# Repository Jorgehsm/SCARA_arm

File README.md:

# SCARA robotic arm
Braço robótico com 4DOF baseado em esp32.

Utiliza motores de passo com redução por correia para movimento e servo MG996r para controle da pinça.

Projeto pessoal em desenvolvimento

## Projeto da placa de circuito
O projeto conta com o design de uma placa de circuitos para conectar o esp32 responsável pela comunicação e controle do robô com a alimentação e drivers dos motores.

## Projeto CAD
A estrutura do robô foi pensada para fabricação por meio de impressão 3D juntamente com fuso trapezoidal e eixos de aço para movimento no eixo Z.

A transmissão para demais movimentos foi feita por meio de correias GT2 e polias impressas

A estrutura conta também com rolamentos para adicionar rigidez e auxíliar nos movimentos.

O projeto conta também com o design de uma garra atuada por meio de um motor servo e mecanismo pinhâo cremalheira para sua abertura e fechamento

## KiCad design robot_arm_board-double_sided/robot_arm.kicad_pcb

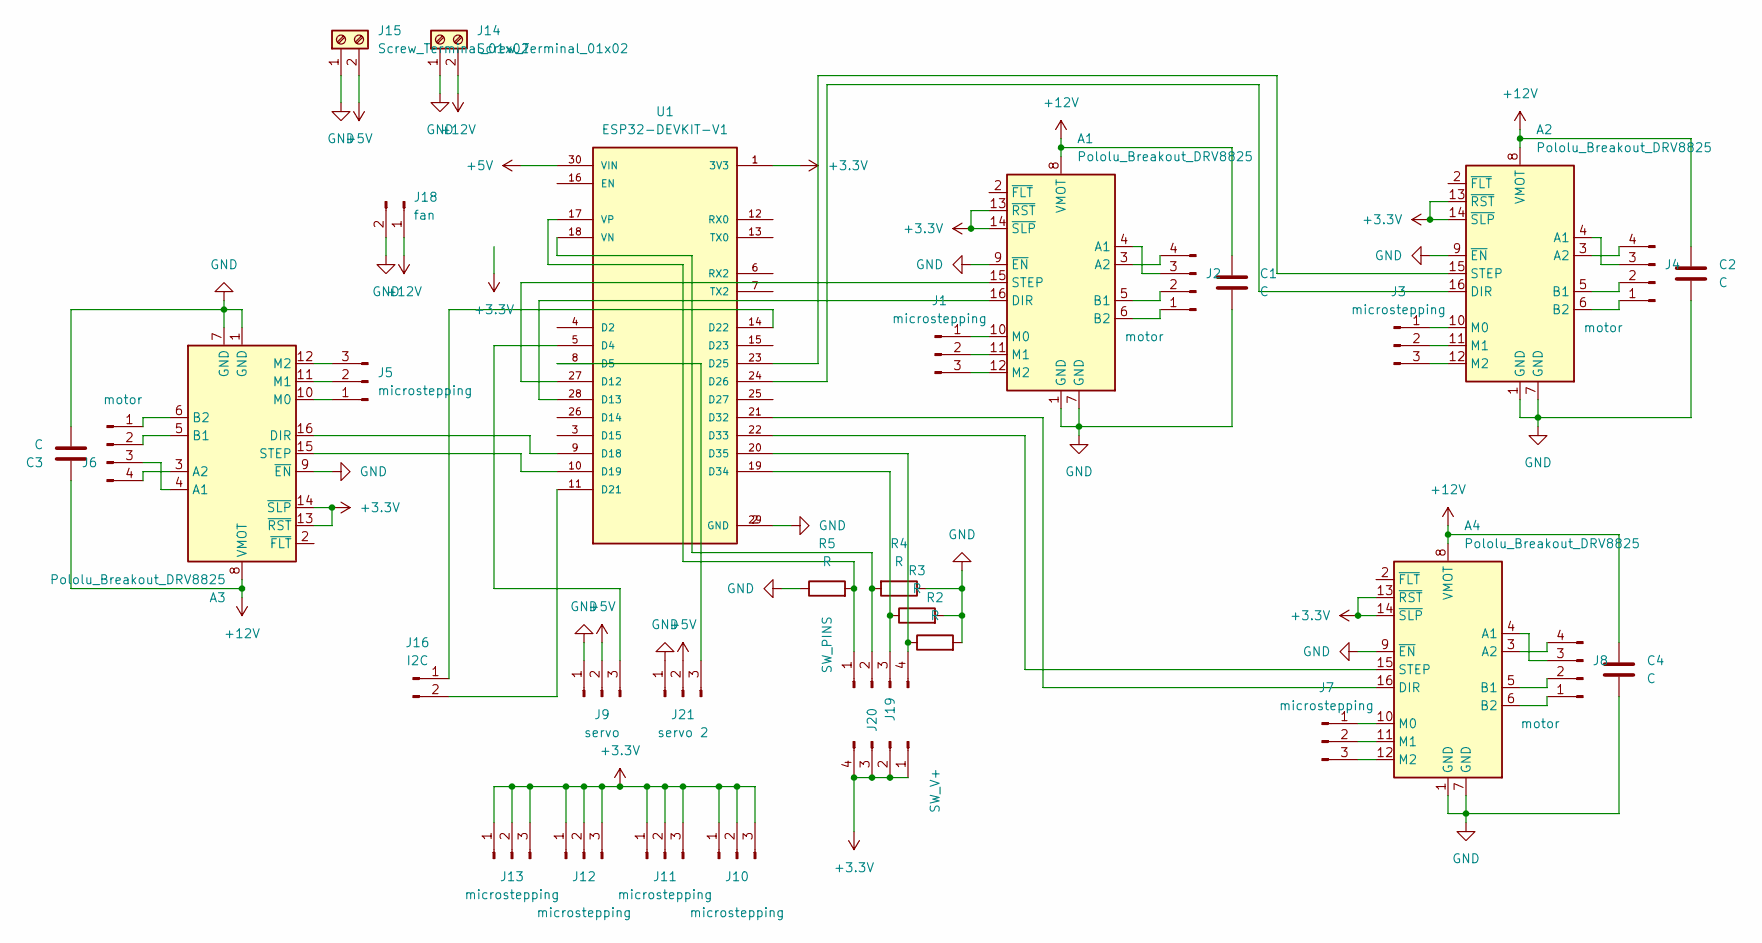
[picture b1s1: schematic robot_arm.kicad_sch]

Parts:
A1, A2, A3, A4: Pololu_Breakout_DRV8825; Pololu_Breakout-16_15.2x20.3mm
C1, C2, C3, C4: C; CP_Radial_D6.3mm_P2.50mm
J1, J3, J5, J7, J10, J11, J12, J13: microstepping; PinHeader_1x03_P2.54mm_Vertical
J2, J4, J6, J8: motor; PinHeader_1x04_P2.54mm_Vertical
J9: servo; PinHeader_1x03_P2.54mm_Vertical
J14, J15: Screw_Terminal_01x02; TerminalBlock_bornier-2_P5.08mm
J16: I2C; PinHeader_1x02_P2.54mm_Vertical
J18: fan; PinHeader_1x02_P2.54mm_Vertical
J19: SW_PINS; PinHeader_1x04_P2.54mm_Vertical
J20: SW_V+; PinHeader_1x04_P2.54mm_Vertical
J21: servo 2; PinHeader_1x03_P2.54mm_Vertical
R2, R3, R4, R5: R; R_Axial_DIN0204_L3.6mm_D1.6mm_P5.08mm_Horizontal
U1: ESP32-DEVKIT-V1; MODULE_ESP32_DEVKIT_V1; PARTREV N/A

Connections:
+3.3V: A1.13 (~RST), A1.14 (~SLP), A2.13 (~RST), A2.14 (~SLP), A3.13 (~RST), A3.14 (~SLP), A4.13 (~RST), A4.14 (~SLP), J10.1, J10.2, J10.3, J11.1, J11.2, J11.3, J12.1, J12.2, J12.3, J13.1, J13.2, J13.3, J20.1, J20.2, J20.3, J20.4, U1.1 (3V3)
+5V: J9.2, J15.2, J21.2, U1.30 (VIN)
+12V: A1.8 (VMOT), A2.8 (VMOT), A3.8 (VMOT), A4.8 (VMOT), C1.1, C2.1, C3.1, C4.1, J14.2, J18.1
GND: A1.1 (GND), A1.7 (GND), A1.9 (~EN), A2.1 (GND), A2.7 (GND), A2.9 (~EN), A3.1 (GND), A3.7 (GND), A3.9 (~EN), A4.1 (GND), A4.7 (GND), A4.9 (~EN), C1.2, C2.2, C3.2, C4.2, J9.1, J14.1, J15.1, J18.2, J21.1, R2.2, R3.2, R4.1, R5.1, U1.2 (GND), U1.29 (GND)
unnamed: A1.4 (A1), J2.3
unnamed: A1.3 (A2), J2.4
unnamed: A1.5 (B1), J2.2
unnamed: A1.6 (B2), J2.1
unnamed: A1.16 (DIR), U1.28 (D13)
unnamed: A1.10 (M0), J1.1
unnamed: A1.11 (M1), J1.2
unnamed: A1.12 (M2), J1.3
unnamed: A1.15 (STEP), U1.27 (D12)
unnamed: A2.4 (A1), J4.3
unnamed: A2.3 (A2), J4.4
unnamed: A2.5 (B1), J4.2
unnamed: A2.6 (B2), J4.1
unnamed: A2.16 (DIR), U1.24 (D26)
unnamed: A2.10 (M0), J3.1
unnamed: A2.11 (M1), J3.2
unnamed: A2.12 (M2), J3.3
unnamed: A2.15 (STEP), U1.23 (D25)
unnamed: A3.4 (A1), J6.3
unnamed: A3.3 (A2), J6.4
unnamed: A3.5 (B1), J6.2
unnamed: A3.6 (B2), J6.1
unnamed: A3.16 (DIR), U1.9 (D18)
unnamed: A3.10 (M0), J5.1
unnamed: A3.11 (M1), J5.2
unnamed: A3.12 (M2), J5.3
unnamed: A3.15 (STEP), U1.10 (D19)
unnamed: A4.4 (A1), J8.3
unnamed: A4.3 (A2), J8.4
unnamed: A4.5 (B1), J8.2
unnamed: A4.6 (B2), J8.1
unnamed: A4.16 (DIR), U1.21 (D32)
unnamed: A4.10 (M0), J7.1
unnamed: A4.11 (M1), J7.2
unnamed: A4.12 (M2), J7.3
unnamed: A4.15 (STEP), U1.22 (D33)
unnamed: J9.3, U1.5 (D4)
unnamed: J16.1, U1.14 (D22)
unnamed: J16.2, U1.11 (D21)
unnamed: J19.1, R5.2, U1.17 (VP)
unnamed: J19.2, R4.2, U1.18 (VN)
unnamed: J19.3, R3.1, U1.19 (D34)
unnamed: J19.4, R2.1, U1.20 (D35)
unnamed: J21.3, U1.8 (D5)

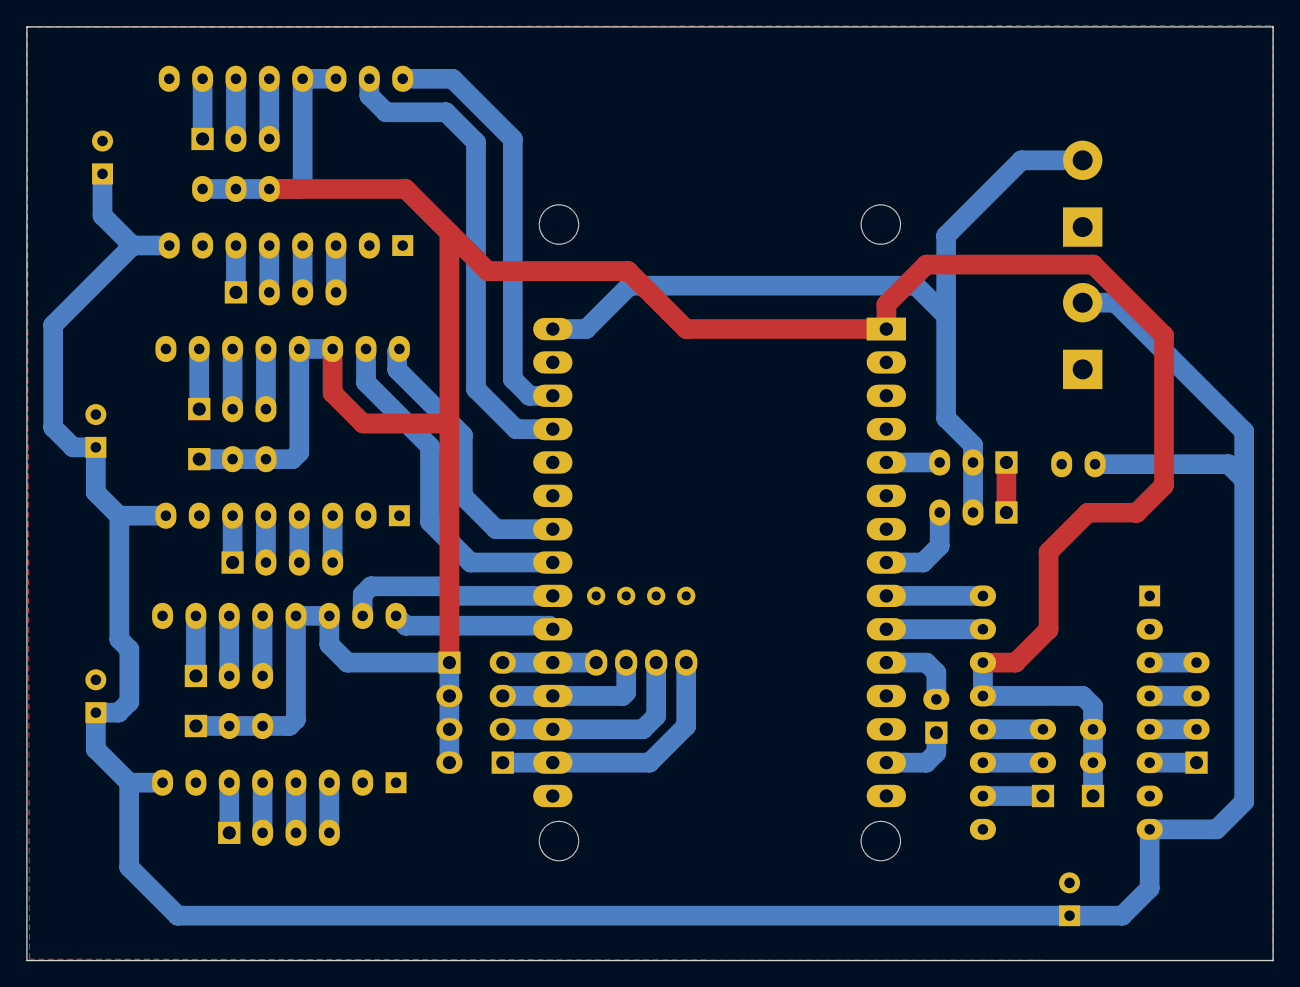
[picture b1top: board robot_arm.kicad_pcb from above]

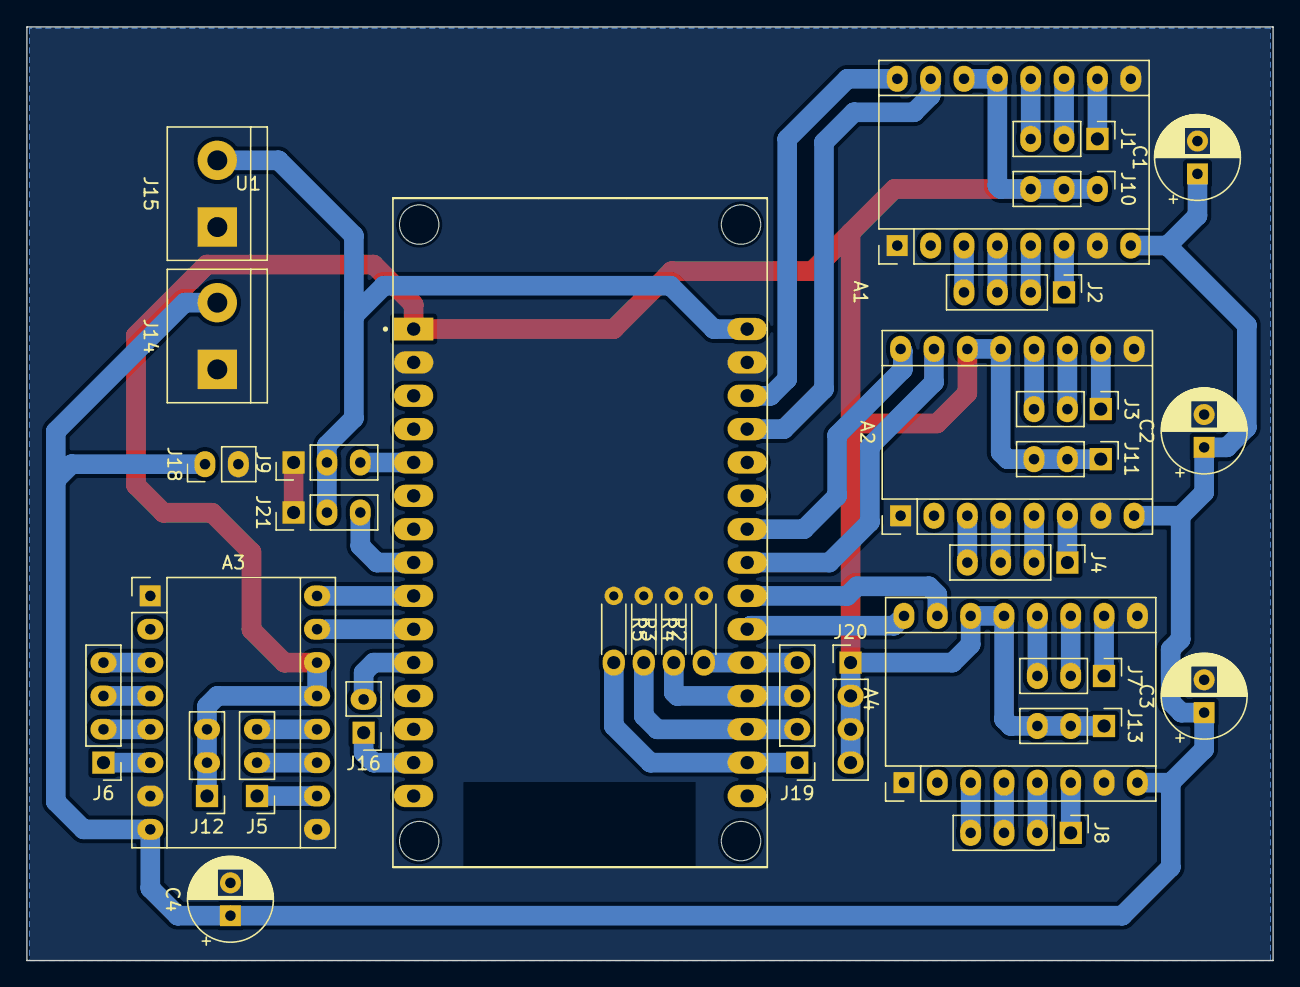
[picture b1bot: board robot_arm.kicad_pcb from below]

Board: 2 copper layers, 94.9 x 71.1 mm, 33 parts (33 on the bottom side), 48 nets.

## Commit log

2024-09-22 Upload arquivos de CAD e PCB
2024-09-22 Mudanças no CAD
2024-11-08 atualizações no modelo
2024-11-08 teste
2025-02-20 Novo modelo e montagem para garra
